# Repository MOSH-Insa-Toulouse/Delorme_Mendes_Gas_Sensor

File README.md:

# KiCad Project

Damaris Mendes Ferreira and Margot Delorme.

### Introduction

In the MOSH (Microcontroller and Open Source Hardware) course we developed a gas sensor shield for an Arduino Uno board. The goal of this project is to construct a PCB that contains a gas sensor, LEDs, a buzzer and a LoRa module. This system should be capable to monitor the level of CO2 in a room and then send this information to a LoRaWAN using The Things Network site. The gas sensor is going to measure the level of CO2 and the Arduino is going to evaluate this level by taking a threshold as comparative. If the quantity of this gas crosses this threshold, a buzzer is activated and a red LED is fired. When the level of gas returns to its normal state, the buzzer is turned off and a green LED is turned on indicating a normal situation.

The followings sections are going to show all the results that we obtained in this project to make the final PCB layout.

### Assemblage and tests

The first step of this project was to assembly all the components on a protoboard to make sure that our system works. In order to validate our circuit and to make sure it works, we first assembled the electronic elements using a protoboard.

After that, we built the communication between our Lora module and The Things Network site. To do that, we added some configurations in the web site. We created our device in the web site, we configured the Device EUI to our Lora module and we configured the code on the Arduino using the Application EUI and the App Key according to the web site. The configurations were done as followed:

Once we made sure the LoRa communication was working, we tested the circuit on the protoboard. We managed to get live information from the circuit to The Things Network site: 

When the CO2 threshold is crossed, the buzzer is activate and the red led is fired. When the CO2 level goes back to normal, the buzzer is stop and the green led is fired. Our circuit was working properly:

The LoRa module send the information about the level of gas to the web site all the time. When the Level of gas is too high, LoRa sends and alert message.

The Arduino code is available in the “Arduino Code” folder. 

### Shield construction on KICAD

To design our PCB, we used the KICAD open-source software that was used to make the electric scheme and the routing for the PCB. The following sections are going to explain the results that we obtained.

#### Complete PCB

First, to create the PCB, we wanted to use as all the listed elements whether mandatory or optional: the leds, the resistances, the capacitors, the buzzer, the LoRa, the amplificator, and all the electronic elements. To do so, we used Kicad and created a first draft of the PCB. So, we drew the graphs and then selected the different items we wanted to use for each element.

The hardest part for us was to place the electronic elements on the PCB and routing it without the routes crossing and using as much as possible only one side of the PCB. For routing, on this first draft we routed on 2 different sides of the PCB.

Once we finished this first version of the PCB, we wanted to go further and have the routing on only one side of the PCB. We used the previous version of our PCB and rearranged it. In order to do this, we had to get rid of a few elements: one led and one button. We chose these 2 elements because the PCB still works without them.

So that you could have an overview of our work, we sent you both PCB. The folder called  “Complete Version” contains the PCB with all the components. The folder called “Final Version” is the latest version of the project. This version of the PCB has just one face of routing (the one abiding by the guidelines) and we are going to show the results of this version in the next sections.

#### Final PCB

##### Schema

First of all, we created the project based into an Arduino UNO template. After that, we started to construct our components. We created the LTC1050 library that is located in the “\MesLibrairies\LTC1050.lib” that is an operational amplifier that is going to be used to amplificate the signal of the gas sensor. After that, we constructed our second library, the RN2483 that is our LORA module. This library is located in the “\MesLibrairies\RN2483.lib”.

Finally, we connected all the elements into a schema as we can see in the following figure.

This schema is called “SchieldProject.sch”. We divided the schema into 5 different blocks. The first one is the circuit to amplificate the signal of the gas sensor. After that we have 2 minors blocks: the buzzer and the LED. The fourth block is composed by the Lora module and to finish we have the Arduino block.

The gas sensor block is composed by a non-inverting amplifier that is going to amplify the analog signal of the gas sensor that is going to be treated by the ADC of the Arduino. The output of the circuit was connected to the A0 pin. The signal is also filtered by this circuit in its entry and in its output to eliminate the noise.

The buzzer was connected into the pin 6 of the Arduino and the LED was connected in the pin 13. For the Lora module, we connected TX in the pin 10, Rx in the pin 11 and RST in the pin 12. This is a really important part of the circuit that is going to enable us to communicate with the TTN (The Things Network).

##### Layout

After doing the circuit schema, we created some footprints that we needed. The first one was the Lora module footprint that is available in the folder “\MesEmpreintes\Module_LoRa_RN2483.kicad_mod”. After that, we modified the footprint of the component TO-5-4 to match the specification of our gas sensor. This footprint is available in the folder “\MesEmpreintes\TO-5-4.kicad_mod”.

Then, we associated the components with their respective footprints and we made the routing of the PCB. The result is shown in the following figure.

3D top view of the PCB:

3D bottom view of the PCB:

### Conclusion

To conclude, we created our PCBs using Kicad, Arduino and The Things Network. We created 2 PCB, one with all the elements (mandatory and optional). Then we created our final version of the PCB thanks to this first draft but using only one side of the PCB. 

What we think could be improved in our PCB is the number of electronic components. We decided to create our final version with only one side of the PCB routed. In order to do so, we got rid of 2 elements.

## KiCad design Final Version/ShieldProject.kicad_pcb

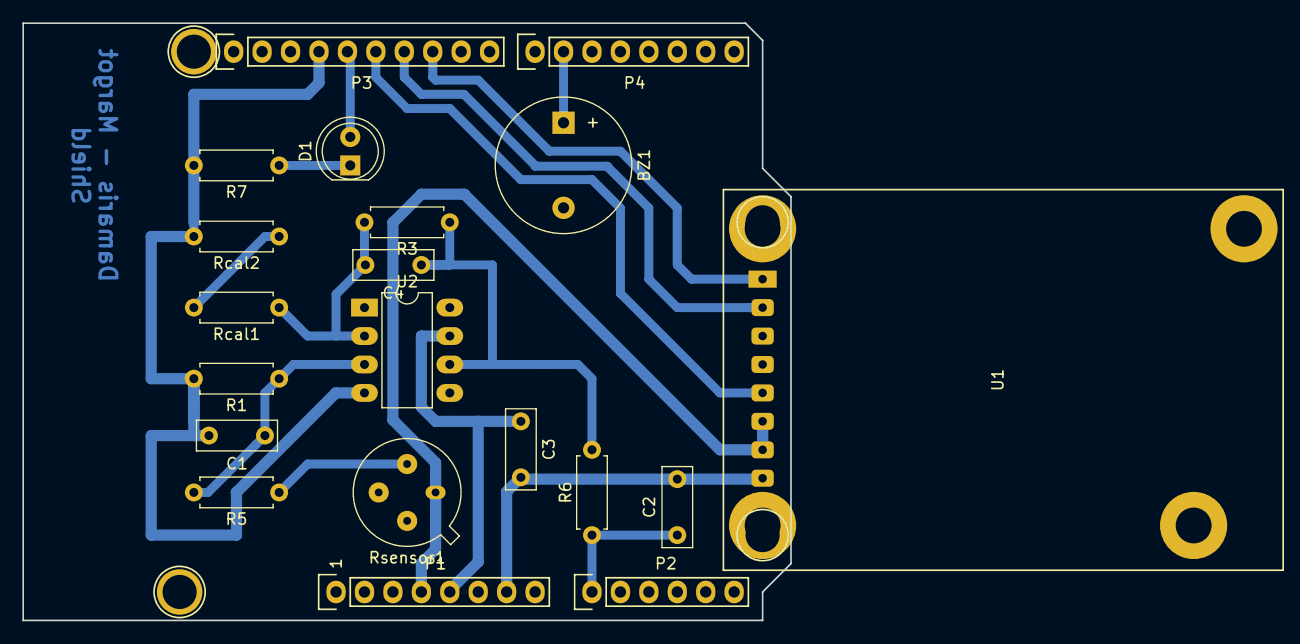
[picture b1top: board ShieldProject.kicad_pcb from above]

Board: 2 copper layers, 68.6 x 53.3 mm, 24 parts (0 on the bottom side), 17 nets.

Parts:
BZ1: Buzzer; Buzzer_12x9.5RM7.6
C1, C2, C3: 100n; C_Rect_L7.0mm_W2.5mm_P5.00mm
C4: 1u; C_Rect_L7.0mm_W2.5mm_P5.00mm
D1: LED; LED_D5.0mm_FlatTop
P1: Power; Socket_Strip_Arduino_1x08
P2: Analog; Socket_Strip_Arduino_1x06
P3: Digital; Socket_Strip_Arduino_1x10
P4: Digital; Socket_Strip_Arduino_1x08
P5, P6, P7, P8: CONN_01X01; Arduino_1pin
R1, R3: 100k; R_Axial_DIN0207_L6.3mm_D2.5mm_P7.62mm_Horizontal
R5, R7: 10k; R_Axial_DIN0207_L6.3mm_D2.5mm_P7.62mm_Horizontal
R6: 1k; R_Axial_DIN0207_L6.3mm_D2.5mm_P7.62mm_Horizontal
Rcal1, Rcal2: R; R_Axial_DIN0207_L6.3mm_D2.5mm_P7.62mm_Horizontal
Rsensor1: 10k; TO-5-4
U1: RN2483_Breakout; Module_LoRa_RN2483
U2: LTC1050; DIP-8_W7.62mm_LongPads

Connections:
+3V3: P1.4, Rsensor1.1, U1.6, U1.7
+5V: C3.1, P1.5, U2.7
/6(**): BZ1.1, P4.2
/10(**/SS): P3.8, U1.1
/11(**/MOSI): P3.7, U1.2
/12(MISO): P3.6, U1.5
/13(SCK): D1.2, P3.5
/A0: C2.1, P2.1, R6.1
/A4(SDA): P2.5, P3.2
/A5(SCL): P2.6, P3.1
GND: BZ1.2, C1.2, C2.2, C3.2, P1.6, P1.7, P3.4, R1.2, R7.2, Rcal2.2, U1.8, U2.4
unnamed: C1.1, R1.1, R5.2, U2.3
unnamed: C4.1, R3.1, R6.2, U2.6
unnamed: C4.2, R3.2, Rcal1.1, U2.2
unnamed: D1.1, R7.1
unnamed: R5.1, Rsensor1.2
unnamed: Rcal1.2, Rcal2.1

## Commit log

2018-11-30 Repo init
2018-11-30 Images
2018-11-30 New image
